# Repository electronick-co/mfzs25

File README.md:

# mfzs25
Repo for the MakerFaire Shenzhen 25 token (SAO) with challenge

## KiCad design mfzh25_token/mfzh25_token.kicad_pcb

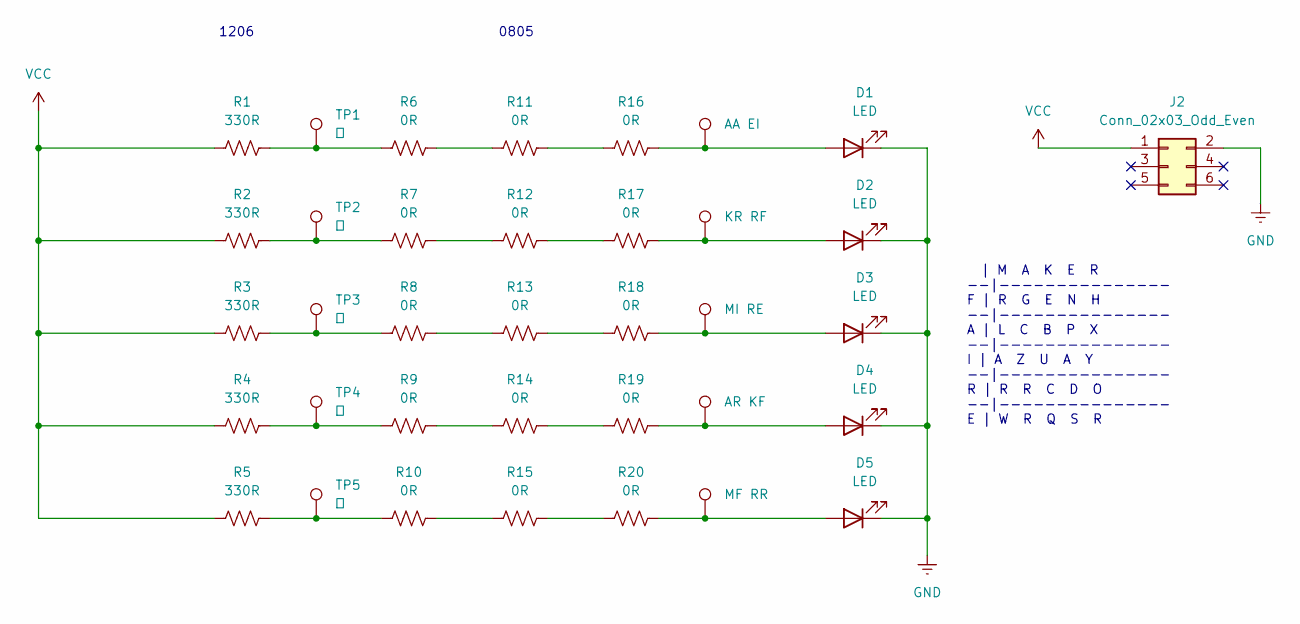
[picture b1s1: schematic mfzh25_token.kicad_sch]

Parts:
D1, D2, D3, D4, D5: LED; LED_1206_3216Metric
J2: Conn_02x03_Odd_Even; IDC-Header_2x03_P2.54mm_Vertical_SMD
R1, R2, R3, R4, R5: 330R; R_1206_3216Metric
R6, R7, R8, R9, R10, R11, R12, R13, R14, R15, R16, R17, R18, R19, R20: 0R; R_0805_2012Metric
TP1: 火; TestPoint_Pad_D1.5mm
TP2: 水; TestPoint_Pad_D1.5mm
TP3: 月; TestPoint_Pad_D1.5mm
TP4: 金; TestPoint_Pad_D1.5mm
TP5: 木; TestPoint_Pad_D1.5mm
TP6: AA EI; TestPoint_Pad_D1.5mm
TP7: KR RF; TestPoint_Pad_D1.5mm
TP8: MI RE; TestPoint_Pad_D1.5mm
TP9: AR KF; TestPoint_Pad_D1.5mm
TP10: MF RR; TestPoint_Pad_D1.5mm

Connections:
GND: D1.1 (K), D2.1 (K), D3.1 (K), D4.1 (K), D5.1 (K), J2.2
unnamed: D1.2 (A), R16.2, TP6.1
unnamed: D2.2 (A), R17.2, TP7.1
unnamed: D3.2 (A), R18.2, TP8.1
unnamed: D4.2 (A), R19.2, TP9.1
unnamed: D5.2 (A), R20.2, TP10.1
unnamed: R1.2, R6.1, TP1.1
unnamed: R2.2, R7.1, TP2.1
unnamed: R3.2, R8.1, TP3.1
unnamed: R4.2, R9.1, TP4.1
unnamed: R5.2, R10.1, TP5.1
unnamed: R10.2, R15.1
unnamed: R6.2, R11.1
unnamed: R11.2, R16.1
unnamed: R7.2, R12.1
unnamed: R12.2, R17.1
unnamed: R8.2, R13.1
unnamed: R13.2, R18.1
unnamed: R9.2, R14.1
unnamed: R14.2, R19.1
unnamed: R15.2, R20.1
VCC: J2.1, R1.1, R2.1, R3.1, R4.1, R5.1

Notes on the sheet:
1206
| M A K E R --|--------------- F | R G E N H --|--------------- A | L C B P X --|--------------- I | A Z U A Y --|--------------- R | R R C D O --|--------------- E | W R Q S R
0805

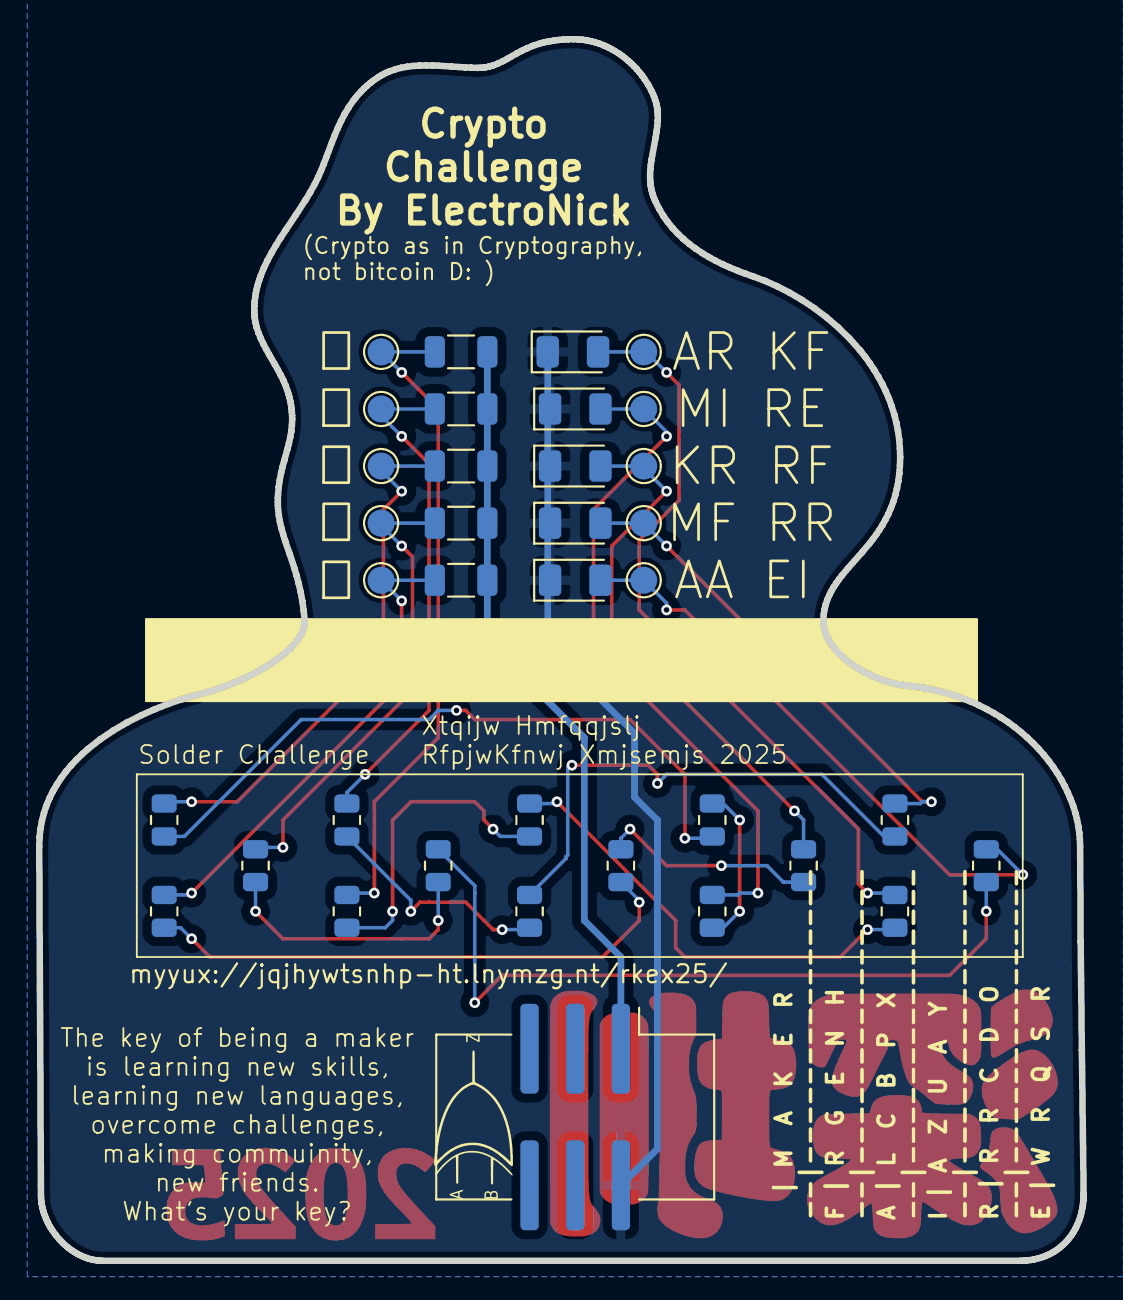
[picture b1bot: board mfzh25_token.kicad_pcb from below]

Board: 2 copper layers, 58.1 x 67.9 mm, 36 parts (36 on the bottom side), 22 nets.

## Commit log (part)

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2025-11-08 first commit. PCB in progress
2025-11-10 almost there
2025-11-10 pcb done, send to fabrication
2025-11-14 webpage done
